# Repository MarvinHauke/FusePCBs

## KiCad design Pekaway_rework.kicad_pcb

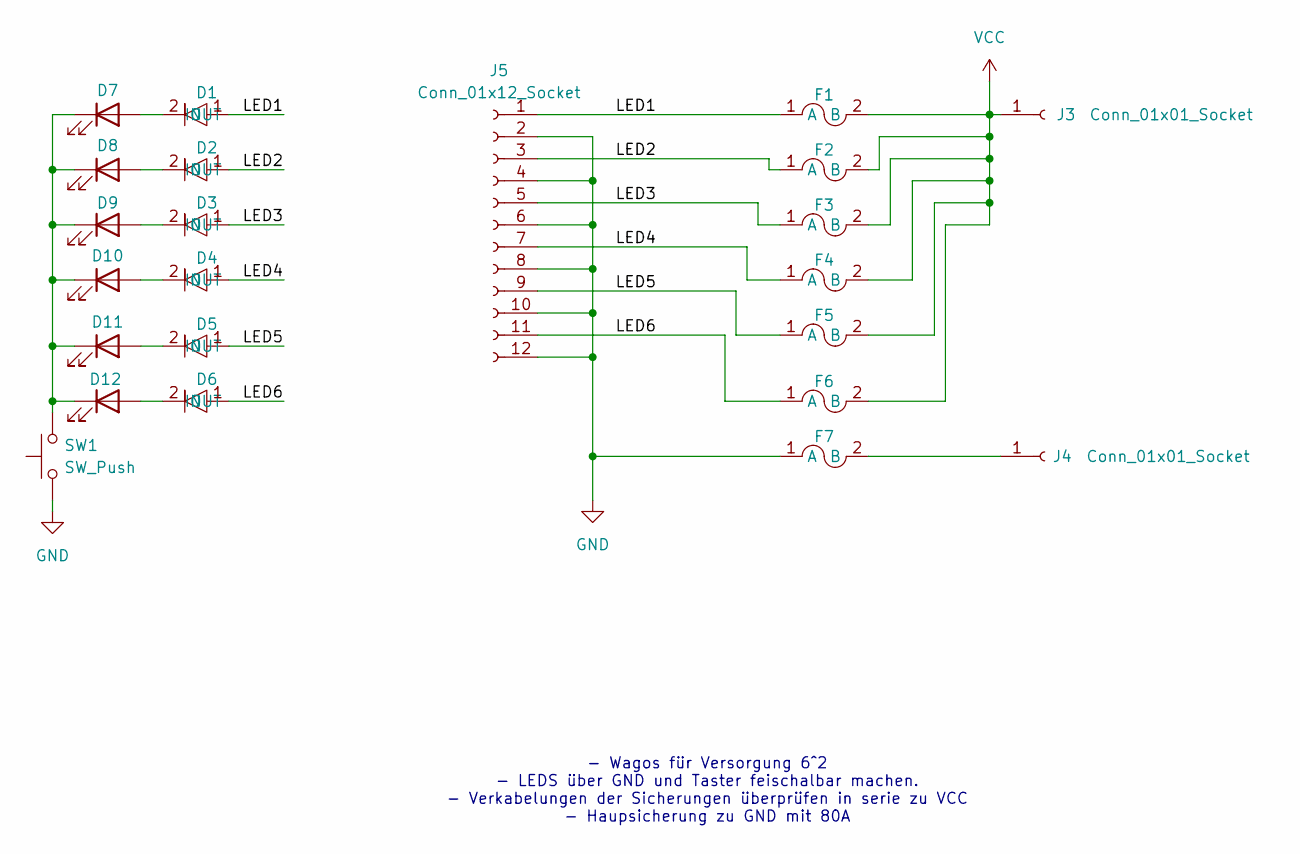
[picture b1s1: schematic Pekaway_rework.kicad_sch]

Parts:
D1, D2, D3, D4, D5, D6: D_SOD-123
D7, D8, D9, D10, D11, D12: LED; LED_0603_1608Metric
F1: Fuse_Blade
F2, F3, F4, F5, F6, F7: Fuse_Blade
J3, J4: Conn_01x01_Socket; CONN_2616-1101_WAG
J5: Conn_01x12_Socket; TerminalBlock_WAGO_2601-3112_1x12_P3.50mm_Vertical
SW1: SW_Push; SW_PUSH_6mm_H4.3mm

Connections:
/LED1: D1.1 (IN), F1.1 (A), J5.1
/LED2: D2.1 (IN), F2.1 (A), J5.3
/LED3: D3.1 (IN), F3.1 (A), J5.5
/LED4: D4.1 (IN), F4.1 (A), J5.7
/LED5: D5.1 (IN), F5.1 (A), J5.9
/LED6: D6.1 (IN), F6.1 (A), J5.11
GND: F7.1 (A), J5.2, J5.4, J5.6, J5.8, J5.10, J5.12, SW1.1
unnamed: D1.2 (OUT), D7.2 (A)
unnamed: D2.2 (OUT), D8.2 (A)
unnamed: D3.2 (OUT), D9.2 (A)
unnamed: D4.2 (OUT), D10.2 (A)
unnamed: D7.1 (K), D8.1 (K), D9.1 (K), D10.1 (K), D11.1 (K), D12.1 (K), SW1.2
unnamed: D5.2 (OUT), D11.2 (A)
unnamed: D6.2 (OUT), D12.2 (A)
unnamed: F7.2 (B), J4.1
VCC: F1.2 (B), F2.2 (B), F3.2 (B), F4.2 (B), F5.2 (B), F6.2 (B), J3.1

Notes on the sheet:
- Wagos für Versorgung 6^2 - LEDS über GND und Taster feischalbar machen. - Verkabelungen der Sicherungen überprüfen in serie zu VCC - Haupsicherung zu GND mit 80A

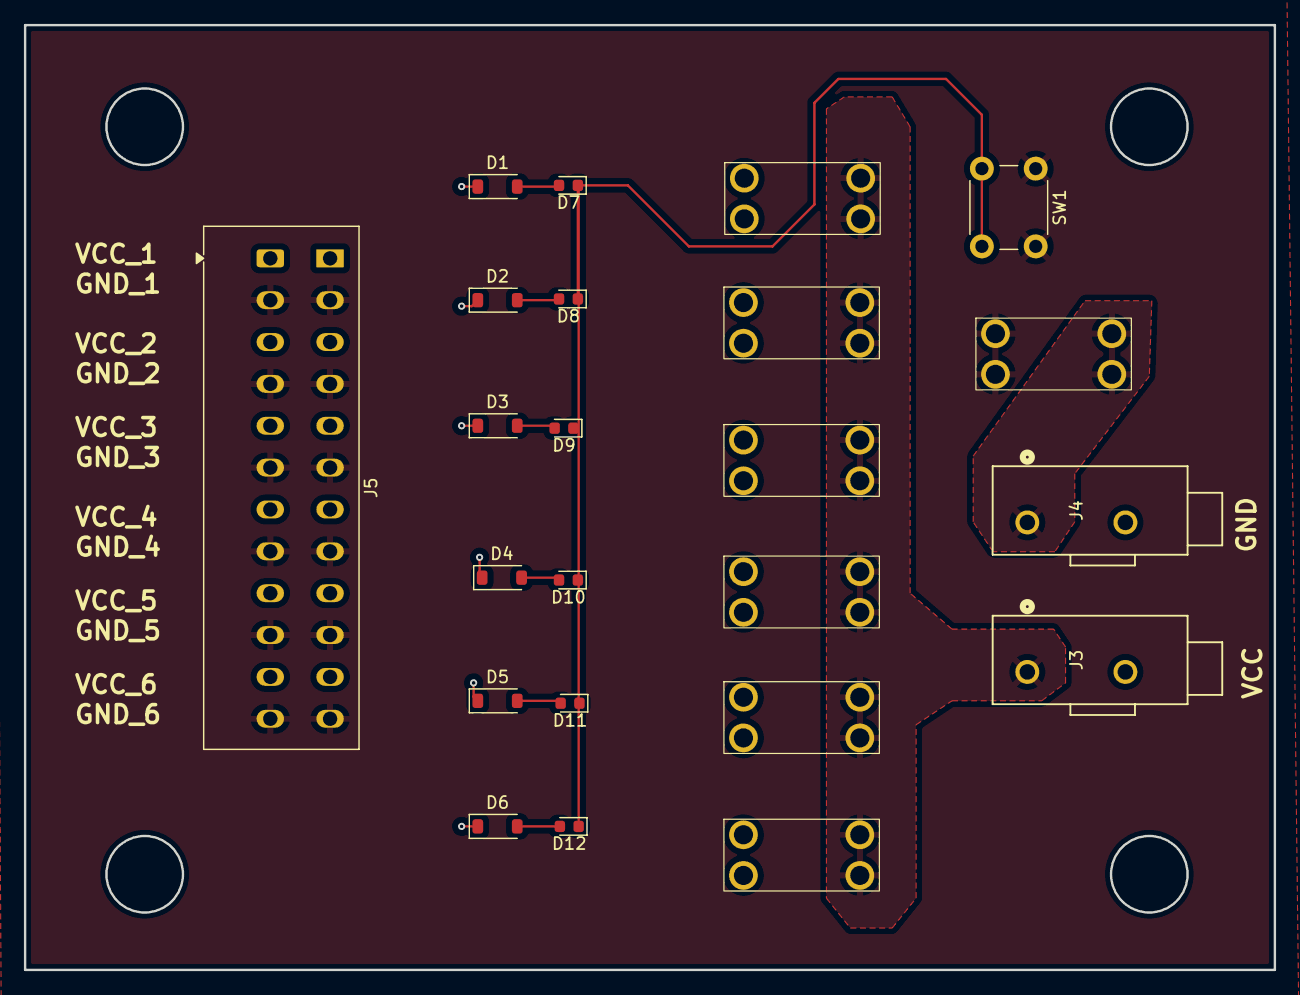
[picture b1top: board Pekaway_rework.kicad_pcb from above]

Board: 2 copper layers, 104.5 x 79.0 mm, 23 parts (0 on the bottom side), 16 nets.

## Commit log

2026-02-08 init commit
2026-02-20 exported gerbers
